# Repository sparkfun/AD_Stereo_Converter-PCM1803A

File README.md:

SparkFun Analog to Digital Stereo Converter Breakout - PCM1803A
===============================================================

[*SparkFun Analog to Digital Stereo Converter Breakout - PCM1803A (BOB-09365)*](https://www.sparkfun.com/products/9365)

The PCM1803A is a high-performance, low-cost, 24-bit stereo analog-to-digital converter that can sample as high as 96k. 
The PCM1803A is a great choice for a wide variety of applications where high performance is necessary. 

Repository Contents
-------------------
* **/Firmware** - Example code 
* **/Hardware** - All Eagle design files (.brd, .sch)

License Information
-------------------
The hardware is released under [Creative Commons ShareAlike 4.0 International](https://creativecommons.org/licenses/by-sa/4.0/).
The code is beerware; if you see me (or any other SparkFun employee) at the local, and you've found our code helpful, please buy us a round!

Distributed as-is; no warranty is given.

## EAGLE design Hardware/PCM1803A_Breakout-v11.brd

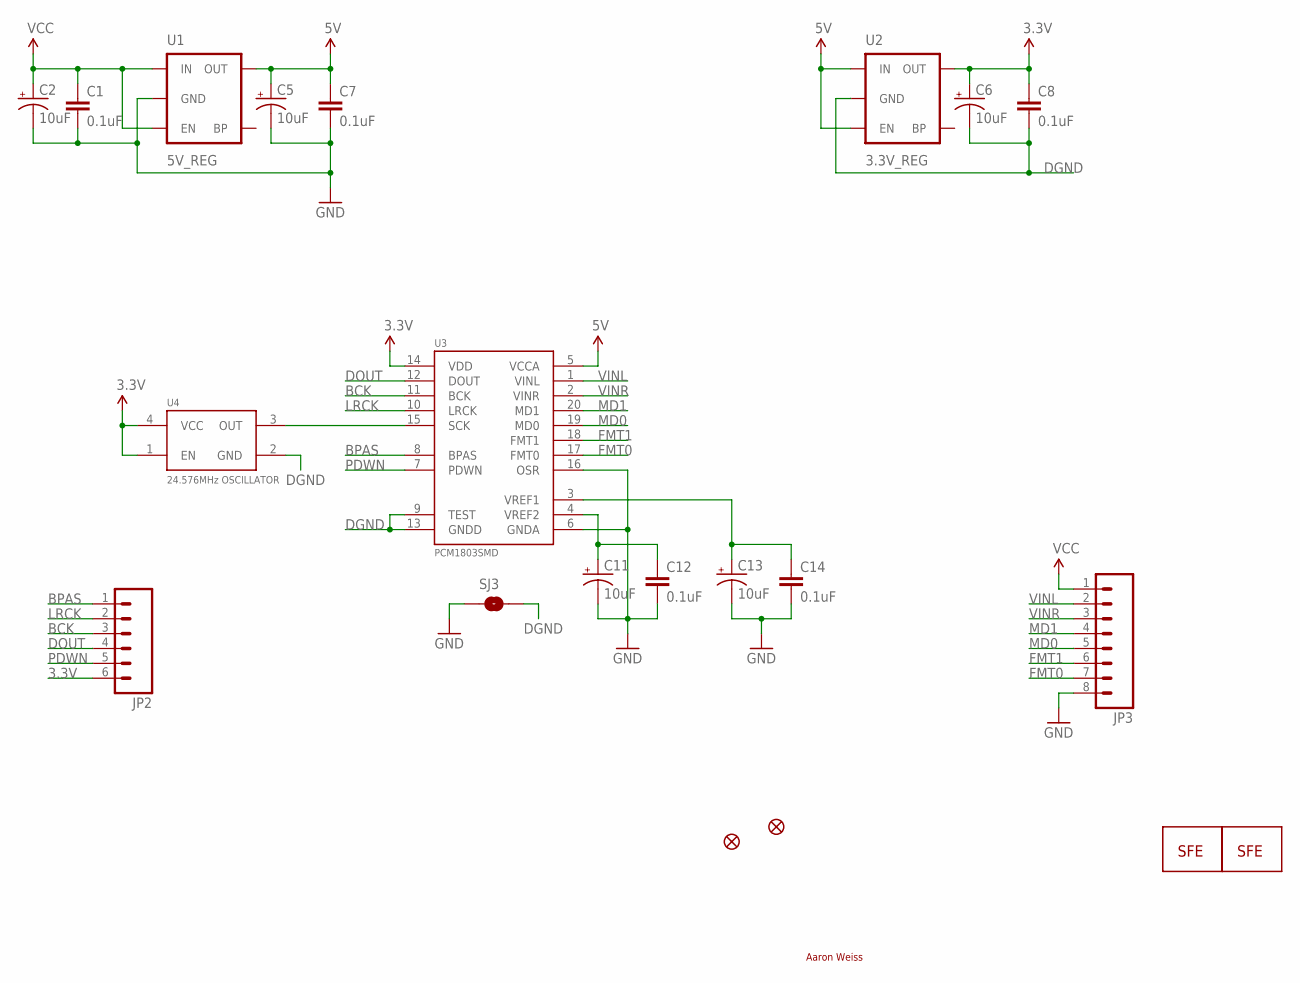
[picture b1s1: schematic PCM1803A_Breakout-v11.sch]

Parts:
C1, C7, C8, C12, C14: 0.1uF; 0402-CAP
C2, C5, C6, C11, C13: 10uF; EIA3216
JP1: LOGO-SFESK; SFE-LOGO-FLAME
JP2: M06SIP; 1X06
JP3: M08; 1X08
JP4, JP5: FIDUCIAL1X2; FIDUCIAL-1X2
SJ3: SOLDERJUMPERTRACE; SJ_2S-TRACE
U1: 5V_REG; SOT23-5
U2: 3.3V_REG; SOT23-5
U3: PCM1803SMD; SSOP20
U4: 24.576MHz OSCILLATOR; CRYSTAL-SMD-7.5X5.2-6PIN
U$4: LOGO-SFENEW; SFE-NEW-WEBLOGO

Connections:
3.3V: C6.A (+), C8.1, JP2.6, U2.5 (OUT), U3.14 (VDD), U4.1 (EN), U4.4 (VCC)
5V: C5.A (+), C7.1, U1.5 (OUT), U2.1 (IN), U2.3 (EN), U3.5 (VCCA)
BCK: JP2.3, U3.11 (BCK)
BPAS: JP2.1, U3.8 (BPAS)
DGND: C6.C (-), C8.2, SJ3.2, U2.2 (GND), U3.9 (TEST), U3.13 (GNDD), U4.2 (GND)
DOUT: JP2.4, U3.12 (DOUT)
FMT0: JP3.7, U3.17 (FMT0)
FMT1: JP3.6, U3.18 (FMT1)
GND: C1.2, C2.C (-), C5.C (-), C7.2, C11.C (-), C12.2, C13.C (-), C14.2, JP3.8, SJ3.1, U1.2 (GND), U3.6 (GNDA), U3.16 (OSR)
LRCK: JP2.2, U3.10 (LRCK)
MD0: JP3.5, U3.19 (MD0)
MD1: JP3.4, U3.20 (MD1)
unnamed: U3.15 (SCK), U4.3 (OUT)
unnamed: C11.A (+), C12.1, U3.4 (VREF2)
unnamed: C13.A (+), C14.1, U3.3 (VREF1)
PDWN: JP2.5, U3.7 (PDWN)
VCC: C1.1, C2.A (+), JP3.1, U1.1 (IN), U1.3 (EN)
VINL: JP3.2, U3.1 (VINL)
VINR: JP3.3, U3.2 (VINR)

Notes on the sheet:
Aaron Weiss

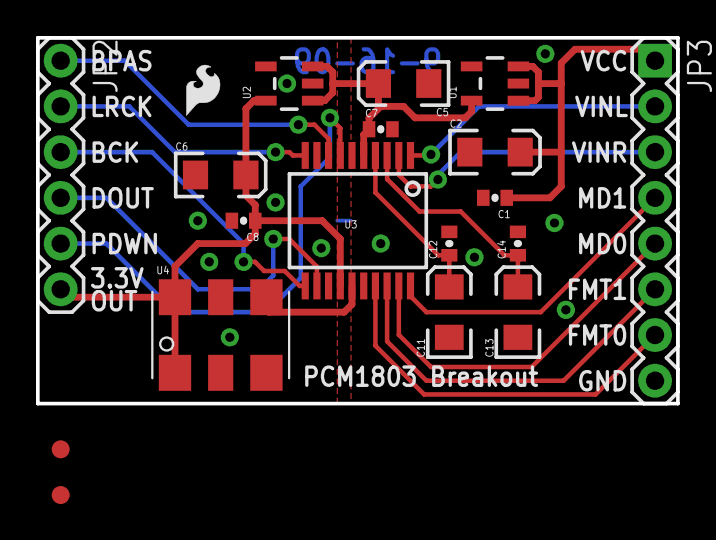
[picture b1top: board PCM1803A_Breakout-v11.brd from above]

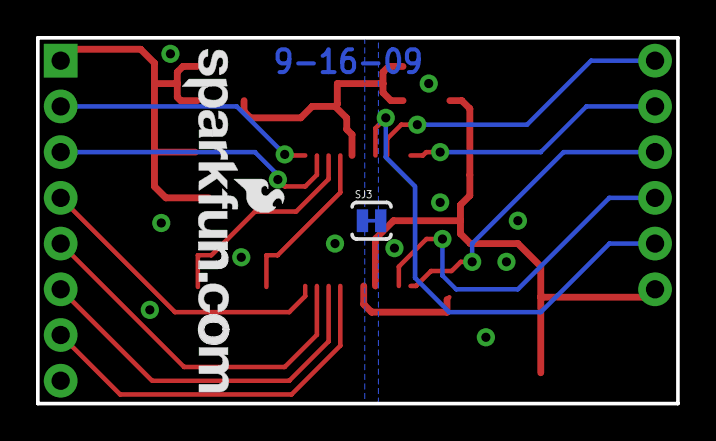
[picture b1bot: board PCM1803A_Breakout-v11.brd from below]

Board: 2 copper layers, 35.6 x 20.3 mm, 21 parts (2 on the bottom side), 19 nets.

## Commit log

2015-03-09 Adding hardware/firmware files, updating readme
